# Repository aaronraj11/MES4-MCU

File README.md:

# MES4-MCU

A small STM32G0B1 microcontroller module with CAN, built as an M.2 2242 (B-key) card.

<p align="center">
  
  &nbsp;&nbsp;&nbsp;
  
</p>

> **Note:** the edge connector uses a custom pinout. This is **not** an M.2 SSD or Wi-Fi card. Do not plug it into a laptop or PC M.2 slot.

## Specifications

| | |
|---|---|
| MCU | STM32G0B1KBT6 (Cortex-M0+, 64 MHz, 128 KB flash, 144 KB RAM), LQFP-32 |
| Clock | 8 MHz oscillator into HSE bypass, PLL to 64 MHz |
| CAN | FDCAN2 + SN65HVD230 transceiver, 500 kbit/s, NUP2105L ESD protection, optional 120 Ω termination (JP1) |
| Power input | 5 V (4.75–5.25 V) on fingers 20/22, about 40 mA typical, 240 mA worst case |
| 3.3 V rail | TLV76733 LDO (1 A), up to 50 mA available on finger 4 |
| Protection | SMF6.0A TVS on the 5 V input |
| I/O on the edge | 14 GPIO (8 of them ADC-capable), I²C, UART, SWD, NRST |
| On board | 4 LEDs (5V red, 3V3 green, CAN white, USR yellow), passive buzzer, 5 V input sense on PB2 |
| PCB | M.2 2242 B-key, 22 × 42 mm, 4 layers, 0.8 mm, ENIG, bevelled gold fingers |
| Operating range | −20 to +70 °C (design target) |

## Edge connector

Odd fingers are on the top side, even fingers on the bottom side. All signals are 3.3 V logic.

| Finger | Signal | Notes |
|---|---|---|
| 1 / 3 | CANH / CANL | to the SN65HVD230 through the ESD diode |
| 4 | +3V3 | **output** from the on-board LDO, max 50 mA; never drive it |
| 6 / 8 | UART TX / RX | USART1 (PA9 / PA10), e.g. ST-Link virtual COM port |
| 7 / 9 | SWDIO / SWCLK | PA13 / PA14 |
| 11 | NRST | pull low only (open-drain) |
| 20, 22 | +5V | power input |
| 23 / 25 | USB D+ / D− | wired to PA12 / PA11, not used in Rev A |
| 29, 31 | PC6, PA8 | GPIO (PA8 can read low during reset) |
| 35 – 49 | PA7 … PA0 | GPIO / ADC IN7 … IN0 (PA4, PA5: 3.6 V max) |
| 51 | PC15 | GPIO, sink only (no LEDs) |
| 53 / 55 | I²C1 SDA / SCL | PB9 / PB8, pull-ups go on the host board |
| 59, 61, 63 | PB6, PB3, PA15 | GPIO |
| all others | GND | |

## Using the module

- **Power:** supply 5 V on fingers 20/22 only. The module makes its own 3.3 V. Power down before inserting or removing it.
- **Programming / debug:** SWD (fingers 7/9/11) with finger 4 as the target voltage reference. The UART on fingers 6/8 is handy as a debug console.
- **CAN termination:** a CAN bus needs exactly two 120 Ω terminators, one at each end of the cable. Bridge solder jumper JP1 only if this module sits at an end. With everything powered off, CANH to CANL should measure about 60 Ω.
- **CAN wiring:** never run CANH/CANL in a connector or cable that also carries more than 12 V. The SN65HVD230 bus pins are rated −4 to +16 V, so a short to a 24 V supply destroys the transceiver (and R7 if JP1 is bridged). Rev A accepts this and relies on the harness.
- **Test points:** GND, 3V3 and 5V pads on the top side.

## Firmware notes

- HSE is an 8 MHz oscillator on PC14 (bypass mode). PLL: M = 2, N = 32, R = 2, Q = 2 → 64 MHz system and FDCAN clock.
- CAN at 500 kbit/s: prescaler 8, 16 time quanta (TSEG1 13, TSEG2 2, SJW 2), sample point 87.5 %.
- Set the UCPD1/UCPD2 strobe bits in SYSCFG early in start-up so PA8 is released.
- The buzzer is passive: drive PB7 with PWM (TIM4_CH2, about 4 kHz) and keep it low when idle, never high.
- Status LEDs: CAN on PB4, USR on PB5. Input voltage sense on PB2 (ADC IN10, divider ×3).

## Repository contents

| File | |
|---|---|
| `MES4-MCU.kicad_pro` | KiCad 9 project |
| `*.kicad_sch` | schematic (overview, power, MCU, CAN / M.2, datasheet links) |
| `MES4-MCU.kicad_pcb` | PCB layout |
| `MES4-MCU.pdf` | schematic as PDF |
| `MES4-MCU-BOM.csv` | bill of materials with LCSC part numbers |
| `MES4-MCU.kicad_dru` | custom design rules (JLCPCB 4-layer) |
| `MES4-MCU.pretty`, `MES4-MCU.3dshapes`, `MES4-MCU.kicad_sym` | project footprints, 3D models and symbols |
| `sim/` | LTspice benches for the power, MCU and CAN sheets (`python3 run_sims.py`, then `python3 make_report.py` → `report.html`) |

## Manufacturing

Designed for JLCPCB:

- 4 layers, 0.8 mm, stackup JLC04081H-3313 (top signal / GND / 3V3 / bottom signal)
- ENIG surface finish, gold fingers with a 20° / 0.3 mm bevel
- Ordered as a single board, panelised by JLC on the order. JLC only bevels gold fingers on boards or panels of at least 50 × 50 mm, so ask for a panel with the fingers on an outer edge, mouse-bite tabs and no V-cut along the fingers.
- Parts are mostly JLC Basic. The BOM lists LCSC numbers for every part.

## Status

Rev A. The design is complete but has not been fabricated or tested yet.

## Author

Aaron Raj Bhatti, Monkey Robotics. [LinkedIn](https://www.linkedin.com/in/aaron-raj-bhatti/)

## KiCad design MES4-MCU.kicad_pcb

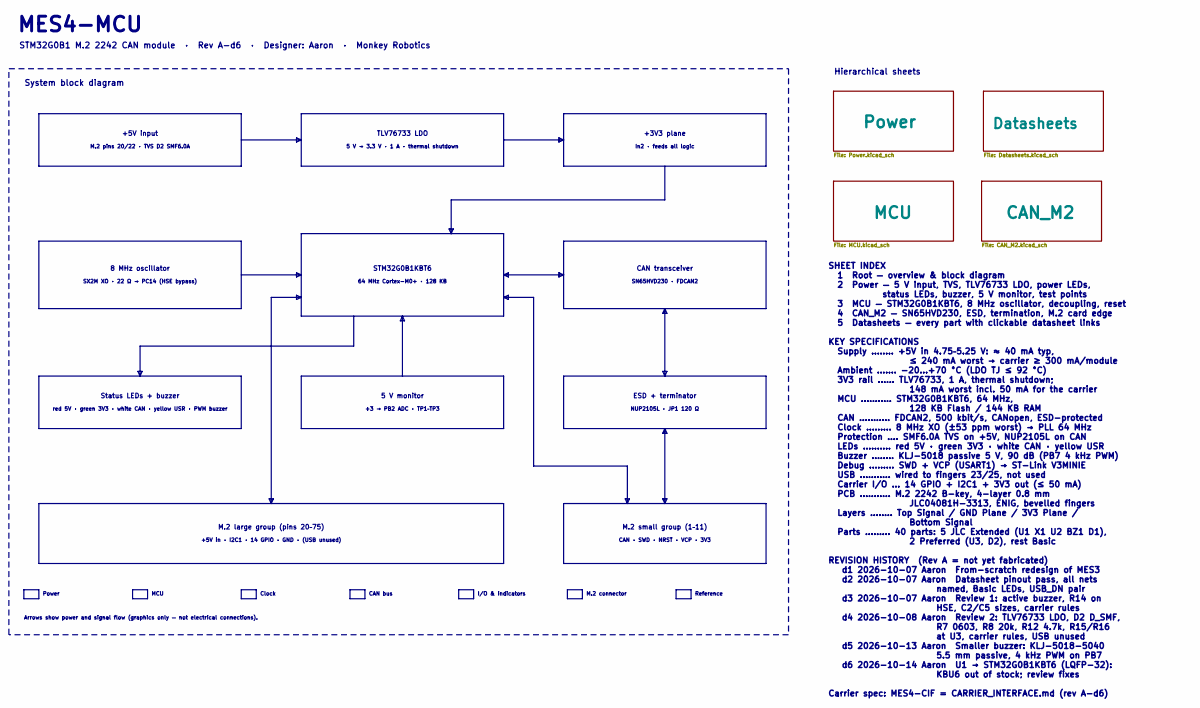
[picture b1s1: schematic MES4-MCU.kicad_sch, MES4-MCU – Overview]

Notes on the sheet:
+5V input
ESD + terminator
CAN transceiver
CAN bus
+5V in · I2C1 · 14 GPIO · GND · (USB unused)
System block diagram
M.2 pins 20/22 · TVS D2 SMF6.0A
NUP2105L · JP1 120 Ω
SX2M XO · 22 Ω → PC14 (HSE bypass)
Status LEDs + buzzer
STM32G0B1 M.2 2242 CAN module · Rev A-d6 · Designer: Aaron · Monkey Robotics
I/O & indicators
SHEET INDEX 1 Root — overview & block diagram 2 Power — 5 V input, TVS, TLV76733 LDO, power LEDs, status LEDs, buzzer, 5 V monitor, test points 3 MCU — STM32G0B1KBT6, 8 MHz oscillator, decoupling, reset 4 CAN_M2 — SN65HVD230, ESD, termination, M.2 card edge 5 Datasheets — every part with clickable 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
M.2 large group (pins 20–75)
TLV76733 LDO
64 MHz Cortex-M0+ · 128 KB
Arrows show power and signal flow (graphics only — not electrical connections).
Reference
STM32G0B1KBT6
SN65HVD230 · FDCAN2
÷3 → PB2 ADC · TP1–TP3
+3V3 plane
M.2 connector
Hierarchical sheets
red 5V · green 3V3 · white CAN · yellow USR · PWM buzzer
5 V monitor
Power
CAN · SWD · NRST · VCP · 3V3
M.2 small group (1–11)
Clock
5 V → 3.3 V · 1 A · thermal shutdown
In2 · feeds all logic
MES4-MCU
8 MHz oscillator
MCU

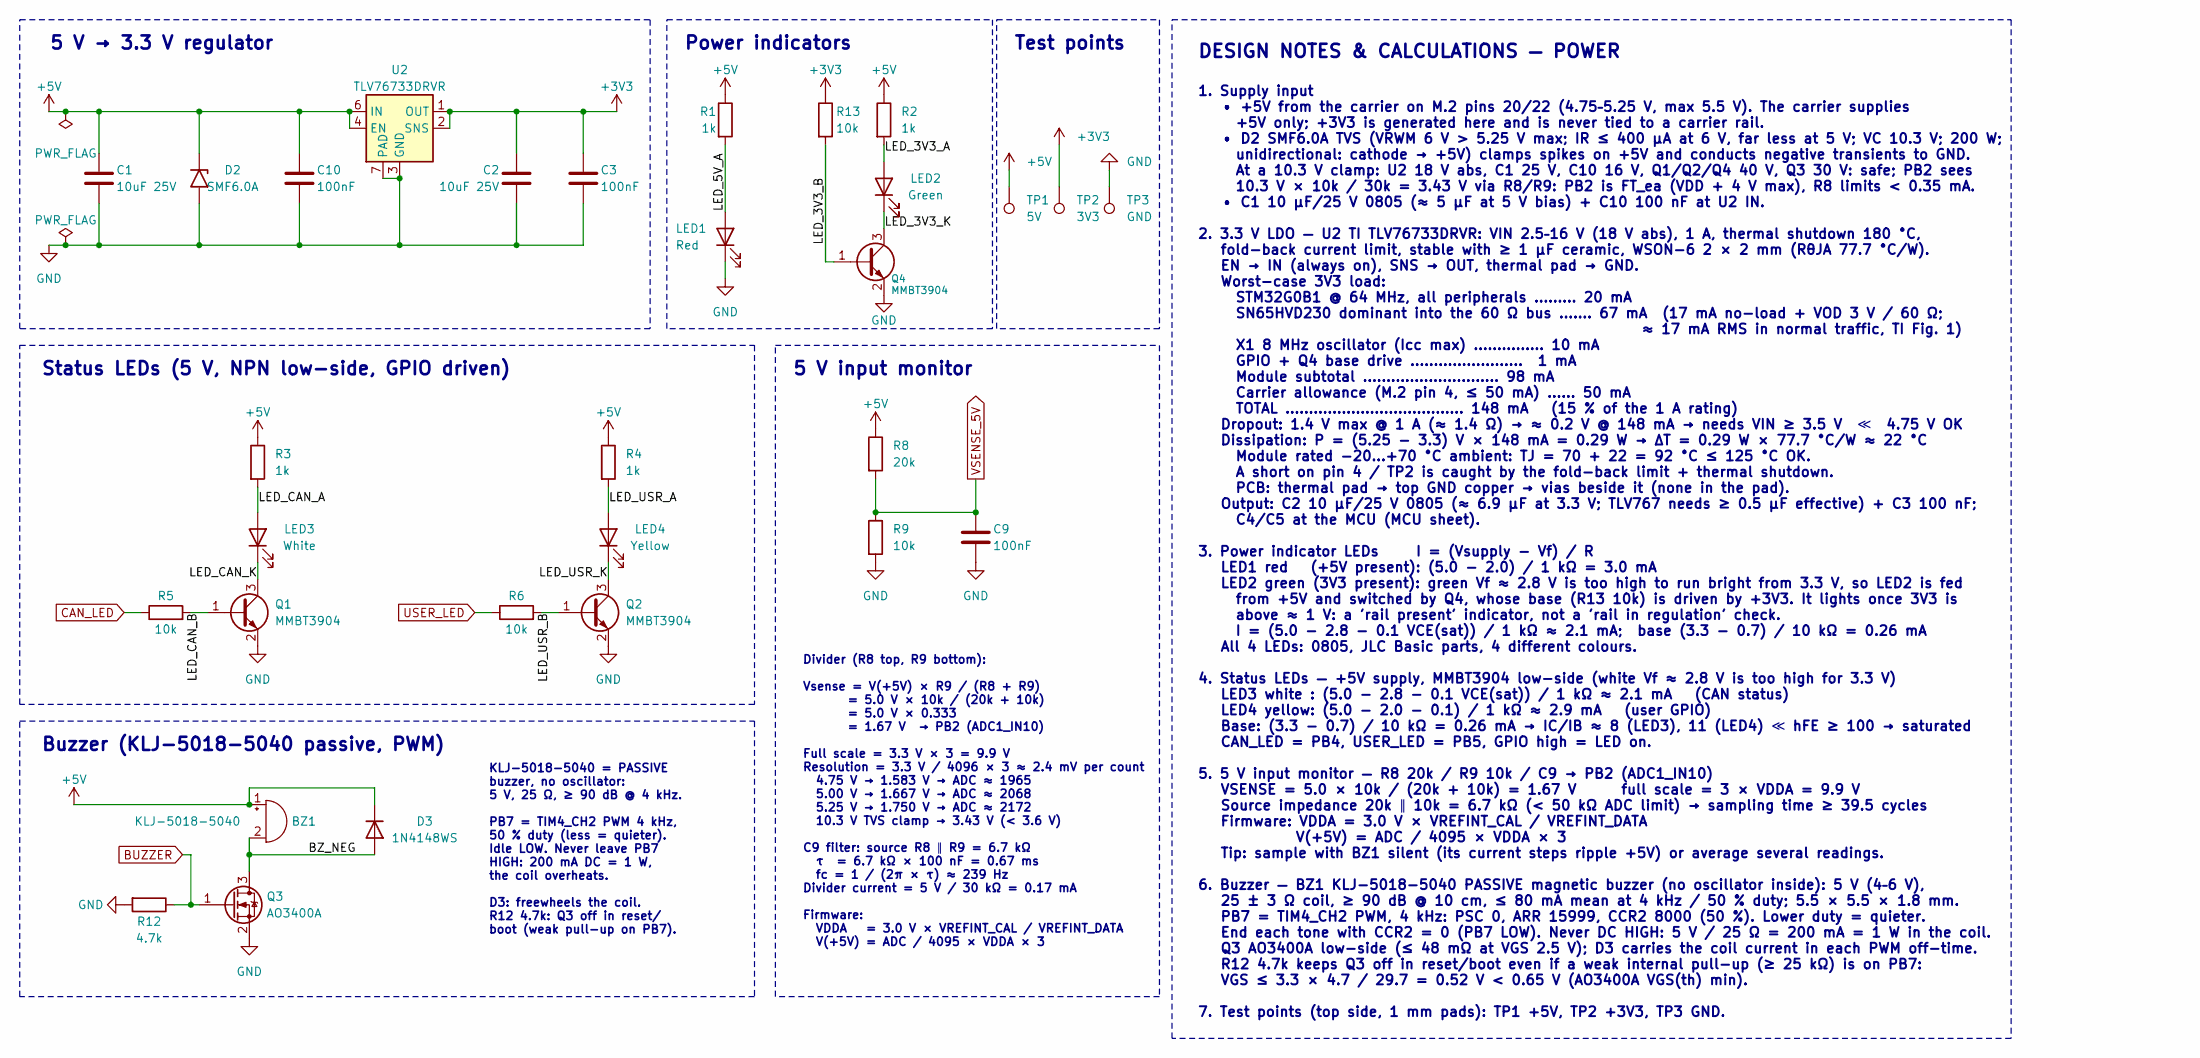
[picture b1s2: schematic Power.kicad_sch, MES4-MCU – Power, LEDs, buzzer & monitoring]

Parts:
BZ1: KLJ-5018-5040; Buzzer_KLJ-5018-5040; MPN KLJ-5018-5040; LCSC C18186309
C1, C2: 10uF 25V; C_0805_2012Metric; MPN CL21A106KAYNNNE; LCSC C15850
C3, C9, C10: 100nF; C_0402_1005Metric; MPN CL05B104KO5NNNC; LCSC C1525
D2: SMF6.0A; D_SMF; MPN SMF6.0A; LCSC C19077499
D3: 1N4148WS; D_SOD-323; MPN 1N4148WS; LCSC C2128
LED1: Red; LED_0805_2012Metric; MPN NCD0805R1; LCSC C84256
LED2: Green; LED_0805_2012Metric; MPN KT-0805G; LCSC C2297
LED3: White; LED_0805_2012Metric; MPN KT-0805W; LCSC C34499
LED4: Yellow; LED_0805_2012Metric; MPN KT-0805Y; LCSC C2296
Q1, Q2, Q4: MMBT3904; SOT-23; MPN MMBT3904; LCSC C20526
Q3: AO3400A; SOT-23; MPN AO3400A; LCSC C20917
R1, R2, R3, R4: 1k; R_0402_1005Metric; MPN 0402WGF1001TCE; LCSC C11702
R5, R6, R9, R13: 10k; R_0402_1005Metric; MPN 0402WGF1002TCE; LCSC C25744
R8: 20k; R_0402_1005Metric; MPN 0402WGF2002TCE; LCSC C25765
R12: 4.7k; R_0402_1005Metric; MPN 0402WGF4701TCE; LCSC C25900
TP1: 5V; TestPoint_Pad_D1.0mm
TP2: 3V3; TestPoint_Pad_D1.0mm
TP3: GND; TestPoint_Pad_D1.0mm
U2: TLV76733DRVR; WSON-6-1EP_2x2mm_P0.65mm_EP1x1.6mm; MPN TLV76733DRVR; LCSC C2848334

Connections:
+3V3: C2.1, C3.1, R13.1, TP2.1, U2.1 (OUT), U2.2 (SNS); also elsewhere on the board
+5V: BZ1.1 (+), C1.1, C10.1, D2.1 (A1), D3.1 (K), R1.1, R2.1, R3.1, R4.1, R8.1, TP1.1, U2.4 (EN), U2.6 (IN); also elsewhere on the board
/Power/BZ_NEG: BZ1.2 (-), D3.2 (A), Q3.3 (D)
/Power/LED_3V3_A: LED2.2 (A), R2.2
/Power/LED_3V3_B: Q4.1 (B), R13.2
/Power/LED_3V3_K: LED2.1 (K), Q4.3 (C)
/Power/LED_5V_A: LED1.2 (A), R1.2
/Power/LED_CAN_A: LED3.2 (A), R3.2
/Power/LED_CAN_B: Q1.1 (B), R5.2
/Power/LED_CAN_K: LED3.1 (K), Q1.3 (C)
/Power/LED_USR_A: LED4.2 (A), R4.2
/Power/LED_USR_B: Q2.1 (B), R6.2
/Power/LED_USR_K: LED4.1 (K), Q2.3 (C)
BUZZER: Q3.1 (G), R12.1; also elsewhere on the board
CAN_LED: R5.1; also elsewhere on the board
GND: C1.2, C2.2, C3.2, C9.2, C10.2, D2.2 (A2), LED1.1 (K), Q1.2 (E), Q2.2 (E), Q3.2 (S), Q4.2 (E), R9.2, R12.2, TP3.1, U2.3 (GND), U2.5 (GND), U2.7 (PAD); also elsewhere on the board
USER_LED: R6.1; also elsewhere on the board
VSENSE_5V: C9.1, R8.2, R9.1; also elsewhere on the board

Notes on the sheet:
5 V input monitor
DESIGN NOTES & CALCULATIONS — POWER
KLJ-5018-5040 = PASSIVE buzzer, no oscillator: 5 V, 25 Ω, ≥ 90 dB @ 4 kHz. PB7 = TIM4_CH2 PWM 4 kHz, 50 % duty (less = quieter). Idle LOW. Never leave PB7 HIGH: 200 mA DC = 1 W, the coil overheats. D3: freewheels the coil. R12 4.7k: Q3 off in reset/ boot (weak pull-up on PB7).
Divider (R8 top, R9 bottom): Vsense = V(+5V) × R9 / (R8 + R9) = 5.0 V × 10k / (20k + 10k) = 5.0 V × 0.333 = 1.67 V → PB2 (ADC1_IN10) Full scale = 3.3 V × 3 = 9.9 V Resolution = 3.3 V / 4096 × 3 ≈ 2.4 mV per count 4.75 V → 1.583 V → ADC ≈ 1965 5.00 V → 1.667 V → ADC ≈ 2068 5.25 V → 1.750 V → ADC ≈ 2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
Status LEDs (5 V, NPN low-side, GPIO driven)
Test points
Power indicators
5 V → 3.3 V regulator
1. Supply input • +5V from the carrier on M.2 pins 20/22 (4.75–5.25 V, max 5.5 V). The carrier supplies +5V only; +3V3 is generated here and is never tied to a carrier rail. • D2 SMF6.0A TVS (VRWM 6 V > 5.25 V max; IR ≤ 400 µA at 6 V, far less at 5 V; VC 10.3 V; 200 W; unidirectional: cathode → +5V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
Buzzer (KLJ-5018-5040 passive, PWM)

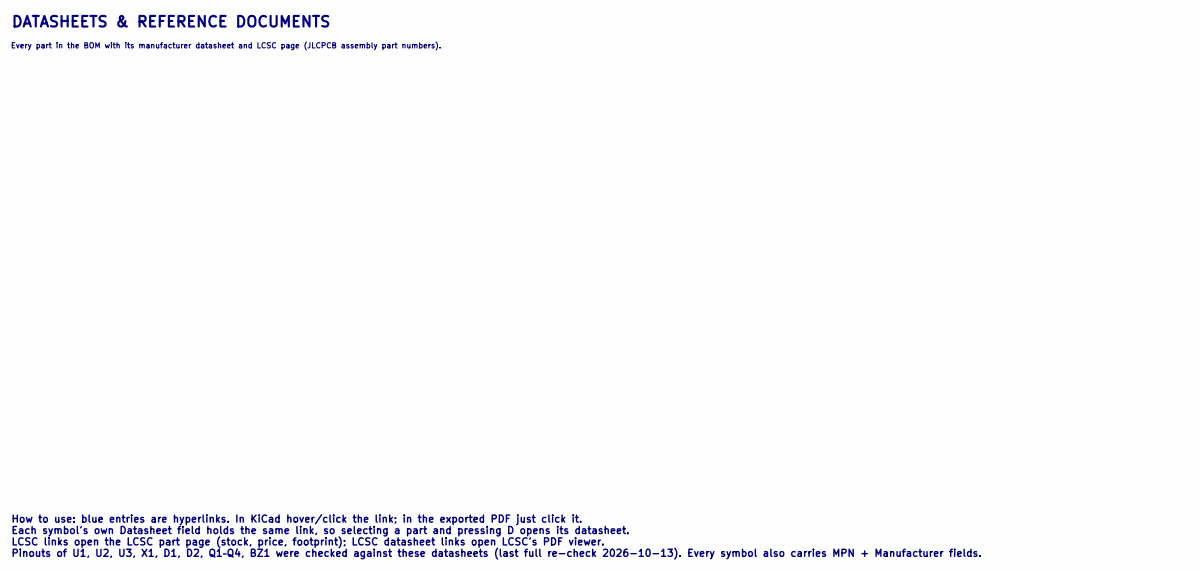
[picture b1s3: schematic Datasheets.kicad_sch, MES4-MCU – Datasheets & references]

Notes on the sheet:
Every part in the BOM with its manufacturer datasheet and LCSC page (JLCPCB assembly part numbers).
DATASHEETS & REFERENCE DOCUMENTS
How to use: blue entries are hyperlinks. In KiCad hover/click the link; in the exported PDF just click it. Each symbol's own Datasheet field holds the same link, so selecting a part and pressing D opens its datasheet. LCSC links open the LCSC part page (stock, price, footprint); LCSC datasheet link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

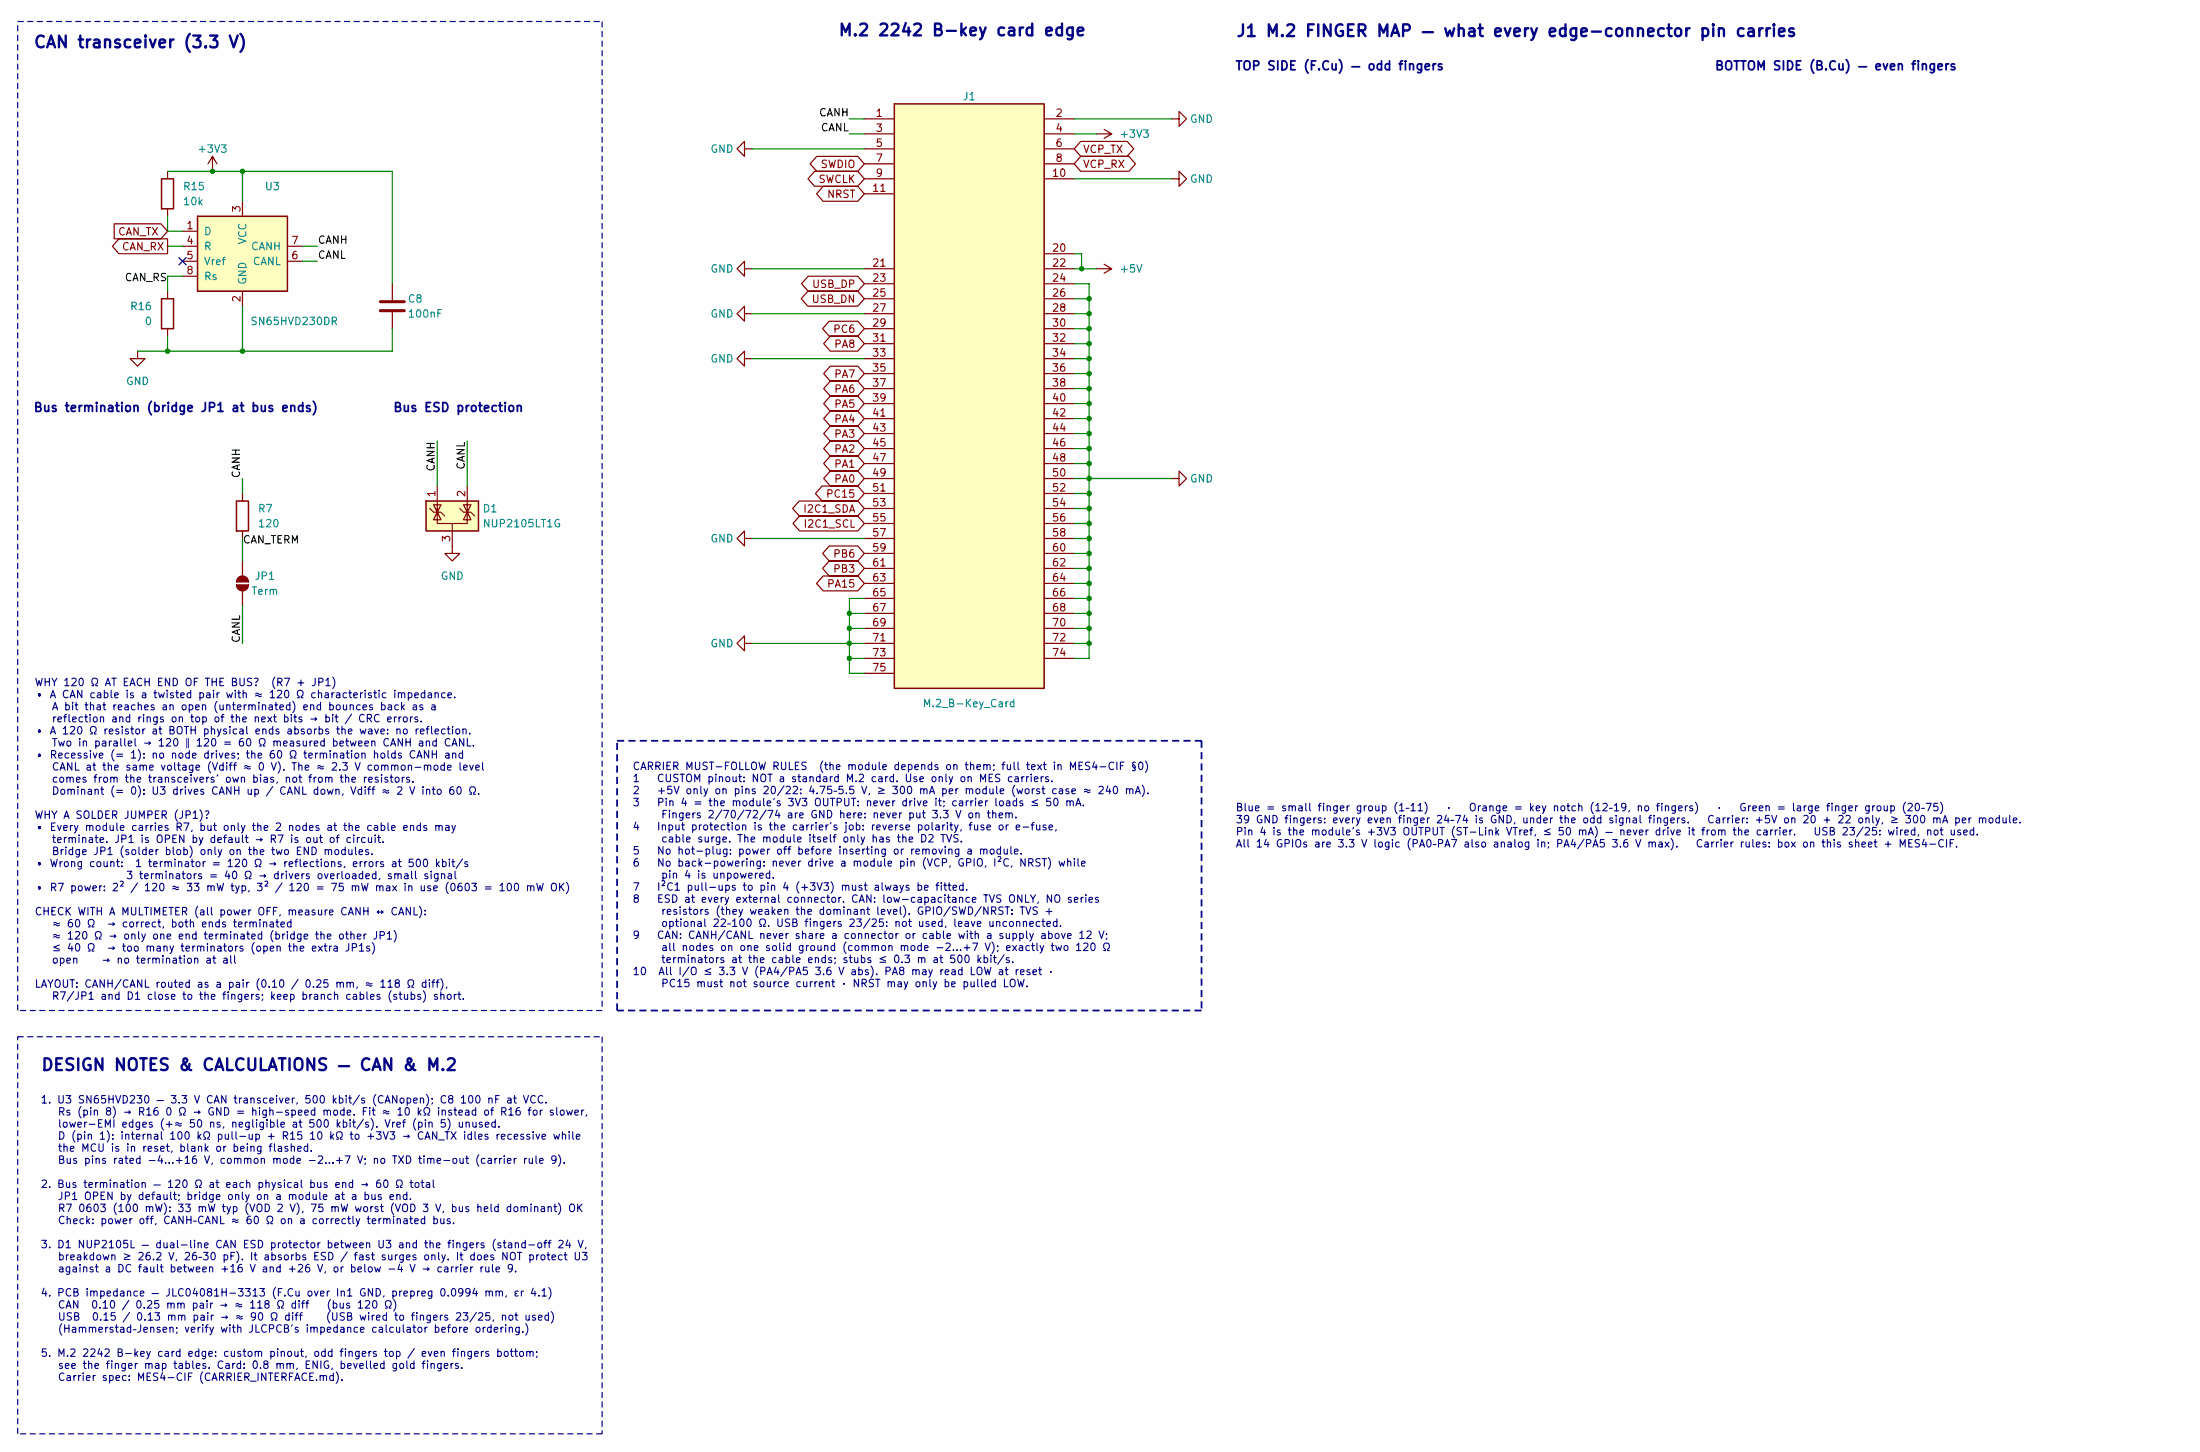
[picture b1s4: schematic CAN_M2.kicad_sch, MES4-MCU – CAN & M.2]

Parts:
C8: 100nF; C_0402_1005Metric; MPN CL05B104KO5NNNC; LCSC C1525
D1: NUP2105LT1G; SOT-23; MPN NUP2105LT1G; LCSC C14486
J1: M.2_B-Key_Card; M.2_2242_B-Key_Card
JP1: Term; SolderJumper-2_P1.3mm_Open_RoundedPad1.0x1.5mm
R7: 120; R_0603_1608Metric; MPN 0603WAF1200T5E; LCSC C22787
R15: 10k; R_0402_1005Metric; MPN 0402WGF1002TCE; LCSC C25744
R16: 0; R_0402_1005Metric; MPN 0402WGF0000TCE; LCSC C17168
U3: SN65HVD230DR; SOIC-8_3.9x4.9mm_P1.27mm; MPN SN65HVD230DR; LCSC C12084

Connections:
+3V3: C8.1, J1.4 (+3V3), R15.1, U3.3 (VCC); also elsewhere on the board
+5V: J1.20 (+5V), J1.22 (+5V); also elsewhere on the board
/CAN_M2/CANH: D1.1 (K), J1.1 (CANH), R7.1, U3.7 (CANH)
/CAN_M2/CANL: D1.2 (K), J1.3 (CANL), JP1.2 (B), U3.6 (CANL)
/CAN_M2/CAN_RS: R16.1, U3.8 (Rs)
/CAN_M2/CAN_TERM: JP1.1 (A), R7.2
CAN_RX: U3.4 (R); also elsewhere on the board
CAN_TX: R15.2, U3.1 (D); also elsewhere on the board
GND: C8.2, D1.3 (A), J1.2 (GND), J1.5 (GND), J1.10 (GND), J1.21 (GND), J1.24 (GND), J1.26 (GND), J1.27 (GND), J1.28 (GND), J1.30 (GND), J1.32 (GND), J1.33 (GND), J1.34 (GND), J1.36 (GND), J1.38 (GND), J1.40 (GND), J1.42 (GND), J1.44 (GND), J1.46 (GND), J1.48 (GND), J1.50 (GND), J1.52 (GND), J1.54 (GND), J1.56 (GND), J1.57 (GND), J1.58 (GND), J1.60 (GND), J1.62 (GND), J1.64 (GND), J1.65 (GND), J1.66 (GND), J1.67 (GND), J1.68 (GND), J1.69 (GND), J1.70 (GND), J1.71 (GND), J1.72 (GND), J1.73 (GND), J1.74 (GND), J1.75 (GND), R16.2, U3.2 (GND); also elsewhere on the board
I2C1_SCL: J1.55 (I2C1_SCL); also elsewhere on the board
I2C1_SDA: J1.53 (I2C1_SDA); also elsewhere on the board
NRST: J1.11 (NRST); also elsewhere on the board
PA0: J1.49 (PA0); also elsewhere on the board
PA1: J1.47 (PA1); also elsewhere on the board
PA2: J1.45 (PA2); also elsewhere on the board
PA3: J1.43 (PA3); also elsewhere on the board
PA4: J1.41 (PA4); also elsewhere on the board
PA5: J1.39 (PA5); also elsewhere on the board
PA6: J1.37 (PA6); also elsewhere on the board
PA7: J1.35 (PA7); also elsewhere on the board
PA8: J1.31 (PA8); also elsewhere on the board
PA15: J1.63 (PA15); also elsewhere on the board
PB3: J1.61 (PB3); also elsewhere on the board
PB6: J1.59 (PB6); also elsewhere on the board
PC6: J1.29 (PC6); also elsewhere on the board
PC15: J1.51 (PC15); also elsewhere on the board
SWCLK: J1.9 (SWCLK); also elsewhere on the board
SWDIO: J1.7 (SWDIO); also elsewhere on the board
USB_DN: J1.25 (USB_DM); also elsewhere on the board
USB_DP: J1.23 (USB_DP); also elsewhere on the board
VCP_RX: J1.8 (VCP_RX); also elsewhere on the board
VCP_TX: J1.6 (VCP_TX); also elsewhere on the board

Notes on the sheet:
Bus ESD protection
Blue = small finger group (1–11) · Orange = key notch (12–19, no fingers) · Green = large finger group (20–75) 39 GND fingers: every even finger 24–74 is GND, under the odd signal fingers. Carrier: +5V on 20 + 22 only, ≥ 300 mA per module. Pin 4 is the module's +3V3 OUTPUT (ST-Link VTref, ≤ 50 mA) 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
DESIGN NOTES & CALCULATIONS — CAN & M.2
J1 M.2 FINGER MAP — what every edge-connector pin carries
CARRIER MUST-FOLLOW RULES (the module depends on them; full text in MES4-CIF §0) 1 CUSTOM pinout: NOT a standard M.2 card. Use only on MES carriers. 2 +5V only on pins 20/22: 4.75–5.5 V, ≥ 300 mA per module (worst case ≈ 240 mA). 3 Pin 4 = the module's 3V3 OUTPUT: never drive it; carrier loads ≤ 50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
TOP SIDE (F.Cu) — odd fingers
WHY 120 Ω AT EACH END OF THE BUS? (R7 + JP1) • A CAN cable is a twisted pair with ≈ 120 Ω characteristic impedance. A bit that reaches an open (unterminated) end bounces back as a reflection and rings on top of the next bits → bit / CRC errors. • A 120 Ω resistor at BOTH physical ends absorbs the w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
M.2 2242 B-key card edge
BOTTOM SIDE (B.Cu) — even fingers
1. U3 SN65HVD230 — 3.3 V CAN transceiver, 500 kbit/s (CANopen); C8 100 nF at VCC. Rs (pin 8) → R16 0 Ω → GND = high-speed mode. Fit ≈ 10 kΩ instead of R16 for slower, lower-EMI edges (+≈ 50 ns, negligible at 500 kbit/s). Vref (pin 5) unused. D (pin 1): internal 100 kΩ pull-up + R15 10 kΩ to +3V3 → 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
CAN transceiver (3.3 V)
Bus termination (bridge JP1 at bus ends)

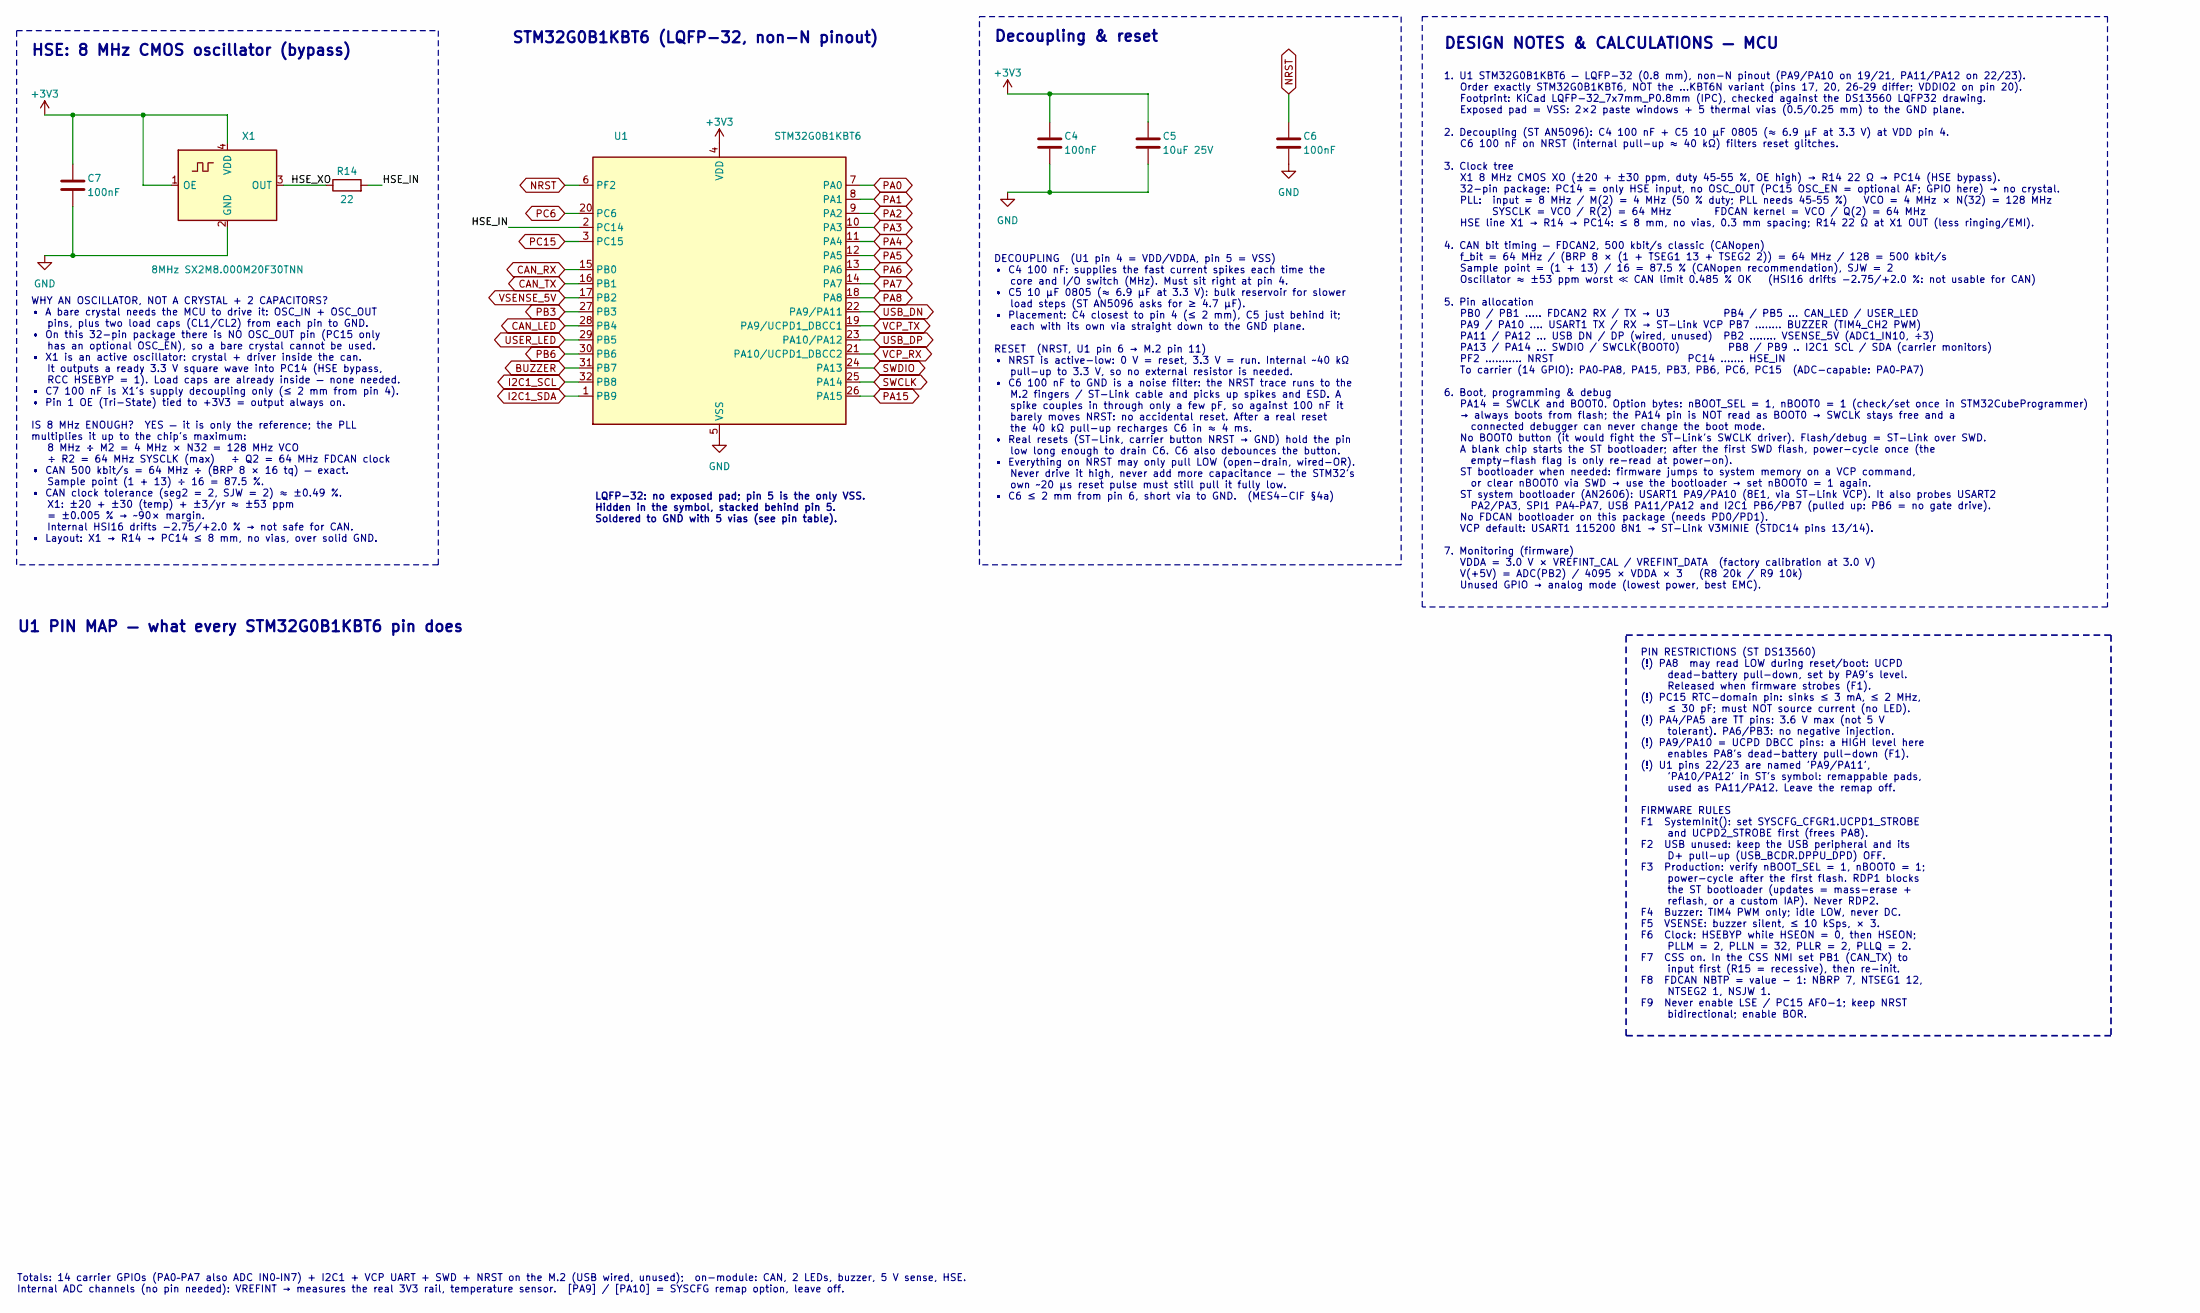
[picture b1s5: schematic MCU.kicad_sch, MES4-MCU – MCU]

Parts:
C4, C6, C7: 100nF; C_0402_1005Metric; MPN CL05B104KO5NNNC; LCSC C1525
C5: 10uF 25V; C_0805_2012Metric; MPN CL21A106KAYNNNE; LCSC C15850
R14: 22; R_0402_1005Metric; MPN 0402WGF220JTCE; LCSC C25092
U1: STM32G0B1KBT6; LQFP-32_7x7mm_P0.8mm; MPN STM32G0B1KBT6; LCSC C5270165
X1: 8MHz SX2M8.000M20F30TNN; Oscillator_SCTF_SX2M_2.5x2.0mm; MPN SX2M8.000M20F30TNN; LCSC C2901594

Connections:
+3V3: C4.1, C5.1, C7.1, U1.4 (VDD), X1.1 (OE), X1.4 (VDD); also elsewhere on the board
/MCU/HSE_IN: R14.2, U1.2 (PC14)
/MCU/HSE_XO: R14.1, X1.3 (OUT)
BUZZER: U1.31 (PB7); also elsewhere on the board
CAN_LED: U1.28 (PB4); also elsewhere on the board
CAN_RX: U1.15 (PB0); also elsewhere on the board
CAN_TX: U1.16 (PB1); also elsewhere on the board
GND: C4.2, C5.2, C6.2, C7.2, U1.5 (VSS), X1.2 (GND); also elsewhere on the board
I2C1_SCL: U1.32 (PB8); also elsewhere on the board
I2C1_SDA: U1.1 (PB9); also elsewhere on the board
NRST: C6.1, U1.6 (PF2); also elsewhere on the board
PA0: U1.7 (PA0); also elsewhere on the board
PA1: U1.8 (PA1); also elsewhere on the board
PA2: U1.9 (PA2); also elsewhere on the board
PA3: U1.10 (PA3); also elsewhere on the board
PA4: U1.11 (PA4); also elsewhere on the board
PA5: U1.12 (PA5); also elsewhere on the board
PA6: U1.13 (PA6); also elsewhere on the board
PA7: U1.14 (PA7); also elsewhere on the board
PA8: U1.18 (PA8); also elsewhere on the board
PA15: U1.26 (PA15); also elsewhere on the board
PB3: U1.27 (PB3); also elsewhere on the board
PB6: U1.30 (PB6); also elsewhere on the board
PC6: U1.20 (PC6); also elsewhere on the board
PC15: U1.3 (PC15); also elsewhere on the board
SWCLK: U1.25 (PA14); also elsewhere on the board
SWDIO: U1.24 (PA13); also elsewhere on the board
USB_DN: U1.22 (PA9/PA11); also elsewhere on the board
USB_DP: U1.23 (PA10/PA12); also elsewhere on the board
USER_LED: U1.29 (PB5); also elsewhere on the board
VCP_RX: U1.21 (PA10/UCPD1_DBCC2); also elsewhere on the board
VCP_TX: U1.19 (PA9/UCPD1_DBCC1); also elsewhere on the board
VSENSE_5V: U1.17 (PB2); also elsewhere on the board

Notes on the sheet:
WHY AN OSCILLATOR, NOT A CRYSTAL + 2 CAPACITORS? • A bare crystal needs the MCU to drive it: OSC_IN + OSC_OUT pins, plus two load caps (CL1/CL2) from each pin to GND. • On this 32-pin package there is NO OSC_OUT pin (PC15 only has an optional OSC_EN), so a bare crystal cannot be used. • X1 is an ac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
LQFP-32: no exposed pad; pin 5 is the only VSS. Hidden in the symbol, stacked behind pin 5. Soldered to GND with 5 vias (see pin table).
1. U1 STM32G0B1KBT6 — LQFP-32 (0.8 mm), non-N pinout (PA9/PA10 on 19/21, PA11/PA12 on 22/23). Order exactly STM32G0B1KBT6, NOT the …KBT6N variant (pins 17, 20, 26–29 differ; VDDIO2 on pin 20). Footprint: KiCad LQFP-32_7x7mm_P0.8mm (IPC), checked against the DS13560 LQFP32 drawing. Exposed pad = VSS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
Decoupling & reset
DESIGN NOTES & CALCULATIONS — MCU
STM32G0B1KBT6 (LQFP-32, non-N pinout)
PIN RESTRICTIONS (ST DS13560) (!) PA8 may read LOW during reset/boot: UCPD dead-battery pull-down, set by PA9's level. Released when firmware strobes (F1). (!) PC15 RTC-domain pin: sinks ≤ 3 mA, ≤ 2 MHz, ≤ 30 pF; must NOT source current (no LED). (!) PA4/PA5 are TT pins: 3.6 V max (not 5 V tolerant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
DECOUPLING (U1 pin 4 = VDD/VDDA, pin 5 = VSS) • C4 100 nF: supplies the fast current spikes each time the core and I/O switch (MHz). Must sit right at pin 4. • C5 10 µF 0805 (≈ 6.9 µF at 3.3 V): bulk reservoir for slower load steps (ST AN5096 asks for ≥ 4.7 µF). • Placement: C4 closest to pin 4 (≤ 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
U1 PIN MAP — what every STM32G0B1KBT6 pin does
Totals: 14 carrier GPIOs (PA0–PA7 also ADC IN0–IN7) + I2C1 + VCP UART + SWD + NRST on the M.2 (USB wired, unused); on-module: CAN, 2 LEDs, buzzer, 5 V sense, HSE. Internal ADC channels (no pin needed): VREFINT → measures the real 3V3 rail, temperature sensor. [PA9] / [PA10] = SYSCFG remap option, l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
HSE: 8 MHz CMOS oscillator (bypass)

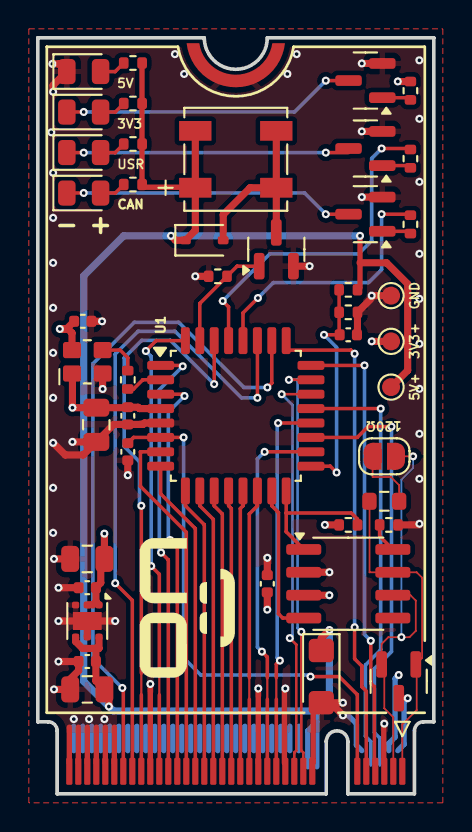
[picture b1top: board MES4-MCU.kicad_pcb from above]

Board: 4 copper layers, 22.0 x 42.0 mm, 46 parts (1 on the bottom side), 49 nets.

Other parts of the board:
LOGO2: KiCad-Logo2_8mm_SilkScreen

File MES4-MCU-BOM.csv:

"Designator","Value","Footprint","LCSC","Qty"
"BZ1","KLJ-5018-5040","MES4-MCU:Buzzer_KLJ-5018-5040","C18186309","1"
"C1,C2,C5","10uF 25V","Capacitor_SMD:C_0805_2012Metric","C15850","3"
"C3,C4,C6,C7,C8,C9,C10","100nF","Capacitor_SMD:C_0402_1005Metric","C1525","7"
"D1","NUP2105LT1G","Package_TO_SOT_SMD:SOT-23","C14486","1"
"D2","SMF6.0A","Diode_SMD:D_SMF","C19077499","1"
"D3","1N4148WS","Diode_SMD:D_SOD-323","C2128","1"
"LED1","Red","LED_SMD:LED_0805_2012Metric","C84256","1"
"LED2","Green","LED_SMD:LED_0805_2012Metric","C2297","1"
"LED3","White","LED_SMD:LED_0805_2012Metric","C34499","1"
"LED4","Yellow","LED_SMD:LED_0805_2012Metric","C2296","1"
"Q1,Q2,Q4","MMBT3904","Package_TO_SOT_SMD:SOT-23","C20526","3"
"Q3","AO3400A","Package_TO_SOT_SMD:SOT-23","C20917","1"
"R1,R2,R3,R4","1k","Resistor_SMD:R_0402_1005Metric","C11702","4"
"R5,R6,R9,R13,R15","10k","Resistor_SMD:R_0402_1005Metric","C25744","5"
"R7","120","Resistor_SMD:R_0603_1608Metric","C22787","1"
"R8","20k","Resistor_SMD:R_0402_1005Metric","C25765","1"
"R12","4.7k","Resistor_SMD:R_0402_1005Metric","C25900","1"
"R14","22","Resistor_SMD:R_0402_1005Metric","C25092","1"
"R16","0","Resistor_SMD:R_0402_1005Metric","C17168","1"
"U1","STM32G0B1KBT6","Package_QFP:LQFP-32_7x7mm_P0.8mm","C5270165","1"
"U2","TLV76733DRVR","Package_SON:WSON-6-1EP_2x2mm_P0.65mm_EP1x1.6mm","C2848334","1"
"U3","SN65HVD230DR","Package_SO:SOIC-8_3.9x4.9mm_P1.27mm","C12084","1"
"X1","8MHz SX2M8.000M20F30TNN","MES4-MCU:Oscillator_SCTF_SX2M_2.5x2.0mm","C2901594","1"

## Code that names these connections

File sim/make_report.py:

"""Build sim/report.html (inline SVG plots) from the LTspice .raw files. Run run_sims.py first."""
import html, math, os
from run_sims import read_raw, read_log, parse_log, HERE

COL = ['#185FA5', '#D85A30', '#1D9E75', '#993556']


def series(d, s):
    """'V(a,b)' = V(a) - V(b); anything else is a column of the raw file."""
    low = {k.lower(): v for k, v in d.items()}  # LTspice writes I(Dl1) for I(DL1)
    if s.lower() in low:
        return low[s.lower()]
    a, b = s[2:-1].split(',')
    return [x - y for x, y in zip(low['v(%s)' % a.lower()], low['v(%s)' % b.lower()])]


def ticklabel(x, span, unit, top=None):
    """Tick label with fixed decimals, enough to tell neighbouring ticks apart. For time axes (unit 's') the
    scale (ms / µs / ns) follows the largest value on the axis (top)."""
    k, u = 1, unit
    if unit == 's':
        m = abs(top) if top is not None else abs(x)
        k, u = (1e3, 'ms') if m >= 1e-3 else (1e6, 'µs') if m >= 1e-6 else (1e9, 'ns')
    dec = max(0, 1 - int(math.floor(math.log10(span * k / 5))))
    return ('%.*f %s' % (dec, x * k, u)).strip()


def plot(name, sigs, t0, t1, title, unit, scale=1.0, limits=(), step=None, steps=None, xunit='s'):
    """sigs on one plot. For a stepped run: step=k plots sigs of step k; steps=[labels] plots sigs[0] for every step."""
    d = read_raw(name)
    if isinstance(d, list):
        if steps is not None:
            runs = [(d[k], sigs[0], lab) for k, lab in enumerate(steps)]
        else:
            runs = [(d[step], s, s) for s in sigs]
    else:
        runs = [(d, s, s) for s in sigs]
    W, H, L, R, T, B = 640, 260, 56, 16, 28, 36
    ser = []
    lo, hi = float('inf'), float('-inf')
    for dd, s, lab in runs:
        t = dd[list(dd)[0]]
        y = series(dd, s)
        pts = [(x, v * scale) for x, v in zip(t, y) if t0 <= x <= t1]
        n = max(1, len(pts) // 350)  # keep min / max per bucket so peaks survive
        red = []
        for k in range(0, len(pts), n):
            b = pts[k:k + n]
            red += [min(b, key=lambda p: p[1]), max(b, key=lambda p: p[1])] if n > 1 else b
        red.sort()
        ser.append((lab, red))
        lo, hi = min(lo, min(p[1] for p in red)), max(hi, max(p[1] for p in red))
    for v, _ in limits:
        lo, hi = min(lo, v), max(hi, v)
    pad = (hi - lo) * 0.08 or 1
    lo, hi = lo - pad, hi + pad
    X = lambda x: L + (x - t0) / (t1 - t0) * (W - L - R)
    Y = lambda v: T + (hi - v) / (hi - lo) * (H - T - B)
    out = ['<svg viewBox="0 0 %d %d" width="100%%" role="img"><title>%s</title>' % (W, H, html.escape(title))]
    for k in range(6):
        v = lo + (hi - lo) * k / 5
        out.append('<line x1="%d" x2="%d" y1="%.1f" y2="%.1f" class="grid"/><text x="%d" y="%.1f" class="ax" text-anchor="end">%s</text>'
                   % (L, W - R, Y(v), Y(v), L - 6, Y(v) + 4, ticklabel(v, hi - lo, '')))
    for k in range(6):
        x = t0 + (t1 - t0) * k / 5
        out.append('<text x="%.1f" y="%d" class="ax" text-anchor="middle">%s</text>' % (X(x), H - B + 16, ticklabel(x, t1 - t0, xunit, max(abs(t0), abs(t1)))))
    for v, lab in limits:
        out.append('<line x1="%d" x2="%d" y1="%.1f" y2="%.1f" class="lim"/><text x="%d" y="%.1f" class="limt" text-anchor="end">%s</text>'
                   % (L, W - R, Y(v), Y(v), W - R - 4, Y(v) - 4, html.escape(lab)))
    lx = L
    for i, (lab, red) in enumerate(ser):
        pts = ' '.join('%.1f,%.1f' % (X(x), Y(v)) for x, v in red)
        out.append('<polyline points="%s" fill="none" stroke="%s" stroke-width="1.4"/>' % (pts, COL[i % 4]))
        out.append('<rect x="%d" y="8" width="10" height="3" fill="%s"/><text x="%d" y="13" class="lg">%s</text>'
                   % (lx, COL[i % 4], lx + 14, html.escape(lab)))
        lx += 24 + 6.2 * len(lab)
    out.append('<text x="12" y="%d" class="ax">%s</text></svg>' % (T - 6, unit))
    return '<figure><figcaption>%s</figcaption>%s</figure>' % (html.escape(title), ''.join(out))


def steps_of(name):
    return parse_log(read_log(name))[1]


if __name__ == '__main__':
    VIL, VIH = (0.99, 'VIL 0.3 × VDD'), (2.31, 'VIH 0.7 × VDD')
    figs = {
        'mdl1': plot('mdl1_tlv767_fit', ['V(out)'], 1.48e-3, 1.68e-3, 'MDL1 · U2 model, 250 → 850 mA → 250 mA at 0.8 A/µs, COUT 1 µF (TI Fig. 7-12: ≈ −120 / +100 mV)', 'V'),
        'pwr1v': plot('pwr1_powerup', ['V(v5)', 'V(v3)'], 0, 3e-3, 'PWR1 · +5V and +3V3, carrier rail ramping in 2 ms', 'V', step=1, limits=[(2.2, 'U2 UVLO 2.2 V')]),
        'pwr1i': plot('pwr1_powerup', ['I(Vjoin)', 'I(Vu2)'], 0, 1e-3, 'PWR1 · module input current and U2 input current, carrier rail ramping in 100 µs', 'A', step=0),
        'pwr2v': plot('pwr2_hotplug', ['V(f5)', 'V(v5)'], 199.5e-6, 207e-6, 'PWR2 · carrier socket (f5) and module +5V when the contact closes at 200 µs', 'V', limits=[(6.67, 'D2 VBR min 6.67 V'), (4.5, '4.5 V')]),
        'pwr2i': plot('pwr2_hotplug', ['I(S_plug)'], 199.5e-6, 203e-6, 'PWR2 · contact current (negative = into the module)', 'A'),
        'pwr3': plot('pwr3_tvs_pulse', ['V(v5)', 'V(v3)', 'V(pb2)'], 0, 16e-3, 'PWR3 · +19.4 A at 1 ms, −19.4 A at 8.5 ms (10/1000 µs)', 'V', limits=[(-0.3, 'VDD abs min −0.3 V')]),
        'pwr4l': plot('pwr4_dc_sweep', ['I(DL1)', 'I(DL2)', 'I(DL3)', 'I(DL4)'], 4.5, 5.5, 'PWR4 · LED currents vs +5V (LED2 green and LED3 white overlap)', 'mA', scale=1e3, xunit='V'),
        'pwr4v': plot('pwr4_dc_sweep', ['V(v3)', 'V(pb2)'], 3.0, 7.5, 'PWR4 · +3V3 at 148 mA and VSENSE_5V vs +5V', 'V', xunit='V', limits=[(3.0, 'U3 VCC min 3.0 V')]),
        'pwr5': plot('pwr5_3v3_load', ['V(v3)'], 0.9e-3, 3.6e-3, 'PWR5 · +3V3: CAN burst 1.0–1.5 ms, +50 mA on pin 4 at 2 ms, both off at 3 ms', 'V'),
        'bz1v': plot('bz1_buzzer_pwm', ['V(bzn)', 'V(pb7)'], 16e-3, 16.6e-3, 'BZ1 · Q3 drain and PB7 (0.3 mH coil)', 'V', step=1),
        'bz1i': plot('bz1_buzzer_pwm', ['I(Lbz)'], 7.9e-3, 19e-3, 'BZ1 · coil current for 0.1 / 0.3 / 1 mH', 'A', steps=['0.1 mH', '0.3 mH', '1 mH']),
        'bz1r': plot('bz1_buzzer_pwm', ['V(pb2)'], 6e-3, 20e-3, 'BZ1 · VSENSE_5V (PB2) while the buzzer runs, 0.3 mH', 'V', step=1),
        'mcu1': plot('mcu1_hse_clock', ['V(pc)'], 142e-9, 162e-9, 'MCU1 · PC14 rising edge with R14 = 0 Ω and 22 Ω (fast X1 corner)', 'V', steps=['R14 0 Ω', 'R14 22 Ω'], limits=[VIL, VIH]),
        'mcu2': plot('mcu2_nrst', ['V(nrst)'], 0, 30e-3, 'MCU2 · NRST for RPU 25 / 40 / 55 kΩ: power-up, 20 µs internal reset at 10 ms, 1 ms button at 20 ms', 'V', steps=['25 kΩ', '40 kΩ', '55 kΩ'], limits=[VIL, VIH]),
        'can1': plot('can1_bus_500k', ['V(ha,la)', 'V(hb,lb)', 'V(s1h,s1l)'], 0, 30e-6, 'CAN1 · differential voltage at module A, far end B and the 3 m stub (typical driver)', 'V', step=0, limits=[(0.9, 'VIT+ max 0.9 V'), (0.5, 'VIT− min 0.5 V')]),
        'can1z': plot('can1_bus_500k', ['V(ha,la)', 'V(hb,lb)', 'V(s1h,s1l)'], 14.9e-6, 15.5e-6, 'CAN1 · dominant → recessive edge at 15 µs (zoom)', 'V', step=0, limits=[(0.5, 'VIT− min 0.5 V')]),
    }
    tpl = open(os.path.join(HERE, 'report_template.html')).read()
    for k, v in figs.items():
        tpl = tpl.replace('{{%s}}' % k, v)
    open(os.path.join(HERE, 'report.html'), 'w').write(tpl)
    print('written report.html')
